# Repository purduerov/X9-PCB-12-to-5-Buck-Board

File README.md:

# X9-PCB-Power-Conversion

The 48V to 12V buck regulator board

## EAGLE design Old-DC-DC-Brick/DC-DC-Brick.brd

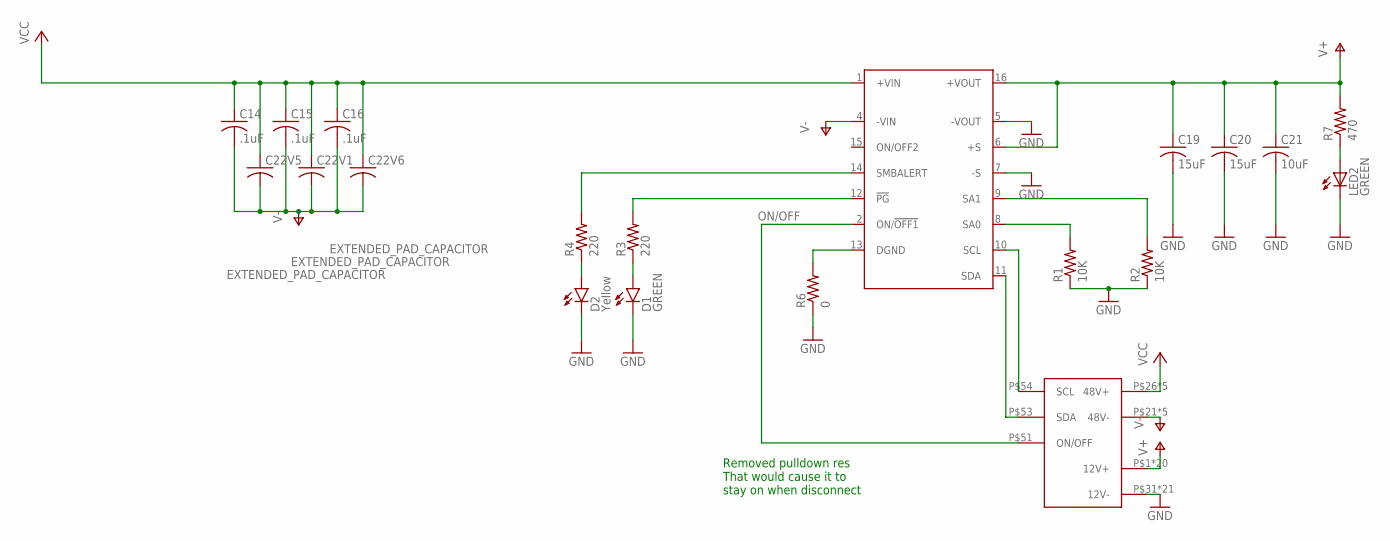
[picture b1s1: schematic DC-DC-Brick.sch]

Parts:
C14, C15, C16: .1uF; C0603
C19, C20: 15uF; C3216
C21: 10uF; C0603
C22V1, C22V5, C22V6: EXTENDED_PAD_CAPACITOR; MODIFIED-NICHICON-UX-8X10
D1: GREEN; LED-0603
D2: Yellow; LED-0603
LED2: GREEN; LED-0603; PARTNO 160-1446-1-ND
R1, R2: 10K; 0603-RES
R3, R4: 220; 0603-RES
R6: 0; 0603-RES
R7: 470; 0603-RES
U$1: BRICK_DC-DC_CONVERTER
U$3: POWER-BRICK-CONNECTOR

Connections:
GND: C19.2, C20.2, C21.2, D1.C, D2.C, LED2.C, R1.1, R2.1, R6.1, U$1.5 (-VOUT), U$1.7 (-S), U$3.P$31 (12V-), U$3.P$32 (12V-), U$3.P$33 (12V-), U$3.P$34 (12V-), U$3.P$35 (12V-), U$3.P$36 (12V-), U$3.P$37 (12V-), U$3.P$38 (12V-), U$3.P$39 (12V-), U$3.P$40 (12V-), U$3.P$41 (12V-), U$3.P$42 (12V-), U$3.P$43 (12V-), U$3.P$44 (12V-), U$3.P$45 (12V-), U$3.P$46 (12V-), U$3.P$47 (12V-), U$3.P$48 (12V-), U$3.P$49 (12V-), U$3.P$50 (12V-), U$3.P$52 (12V-)
unnamed: R2.2, U$1.9 (SA1)
unnamed: R1.2, U$1.8 (SA0)
unnamed: R6.2, U$1.13 (DGND)
unnamed: D1.A, R3.1
unnamed: D2.A, R4.1
unnamed: R4.2, U$1.14 (SMBALERT)
unnamed: R3.2, U$1.12 (!PG)
unnamed: U$1.11 (SDA), U$3.P$53 (SDA)
unnamed: U$1.10 (SCL), U$3.P$54 (SCL)
unnamed: LED2.A, R7.1
ON/OFF: U$1.2 (ON/!OFF1), U$3.P$51 (ON/OFF)
V+: C19.1, C20.1, C21.1, R7.2, U$1.6 (+S), U$1.16 (+VOUT), U$3.P$1 (12V+), U$3.P$2 (12V+), U$3.P$3 (12V+), U$3.P$4 (12V+), U$3.P$5 (12V+), U$3.P$6 (12V+), U$3.P$7 (12V+), U$3.P$8 (12V+), U$3.P$9 (12V+), U$3.P$10 (12V+), U$3.P$11 (12V+), U$3.P$12 (12V+), U$3.P$13 (12V+), U$3.P$14 (12V+), U$3.P$15 (12V+), U$3.P$16 (12V+), U$3.P$17 (12V+), U$3.P$18 (12V+), U$3.P$19 (12V+), U$3.P$20 (12V+)
V-: C14.2, C15.2, C16.2, C22V1.P$1 (4), C22V5.P$1 (4), C22V6.P$1 (4), U$1.4 (-VIN), U$3.P$21 (48V-), U$3.P$22 (48V-), U$3.P$23 (48V-), U$3.P$24 (48V-), U$3.P$25 (48V-)
VCC: C14.1, C15.1, C16.1, C22V1.P$3 (3), C22V5.P$3 (3), C22V6.P$3 (3), U$1.1 (+VIN), U$3.P$26 (48V+), U$3.P$27 (48V+), U$3.P$28 (48V+), U$3.P$29 (48V+), U$3.P$30 (48V+)

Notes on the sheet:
Removed pulldown res That would cause it to stay on when disconnect

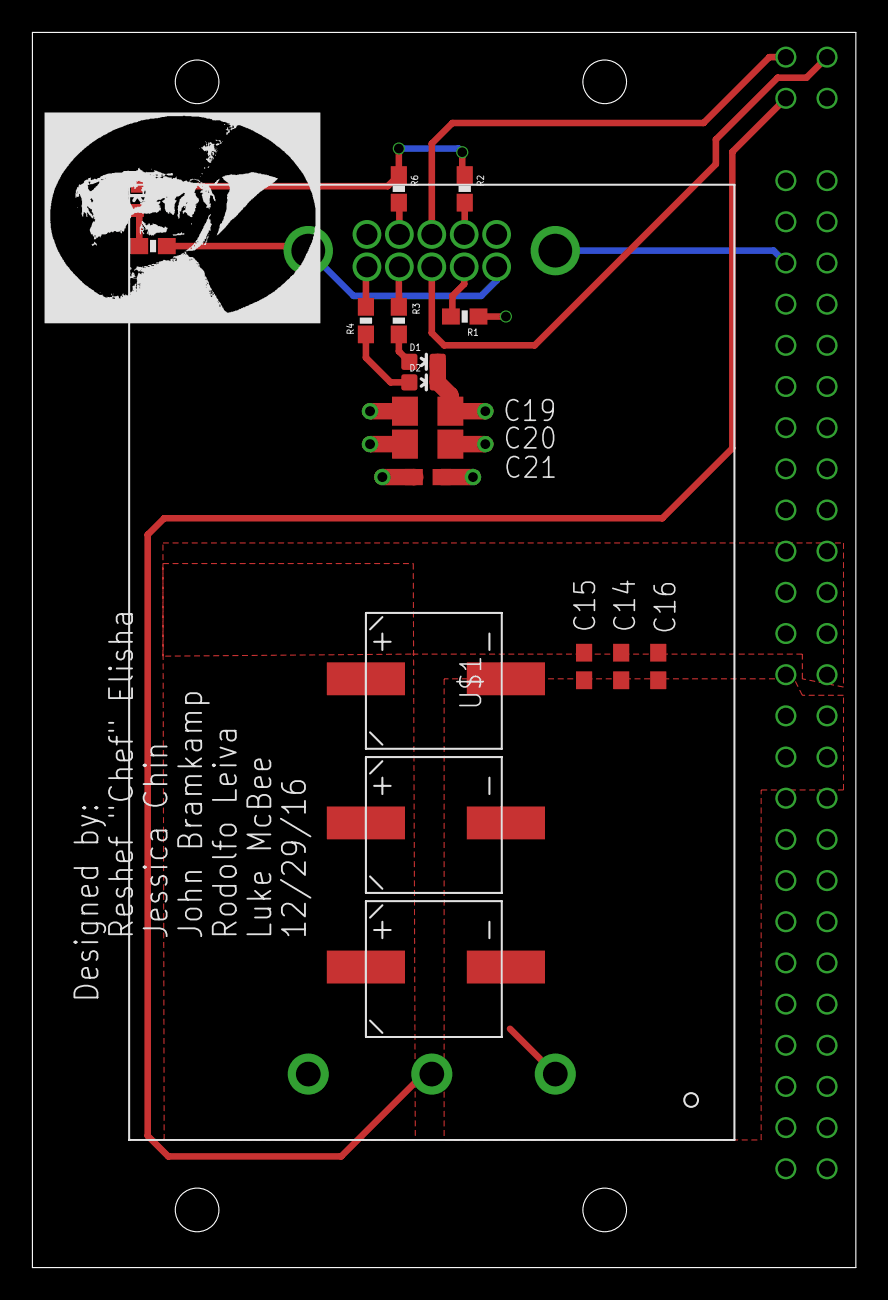
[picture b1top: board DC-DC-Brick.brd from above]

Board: 2 copper layers, 50.8 x 76.2 mm, 20 parts (0 on the bottom side), 15 nets.

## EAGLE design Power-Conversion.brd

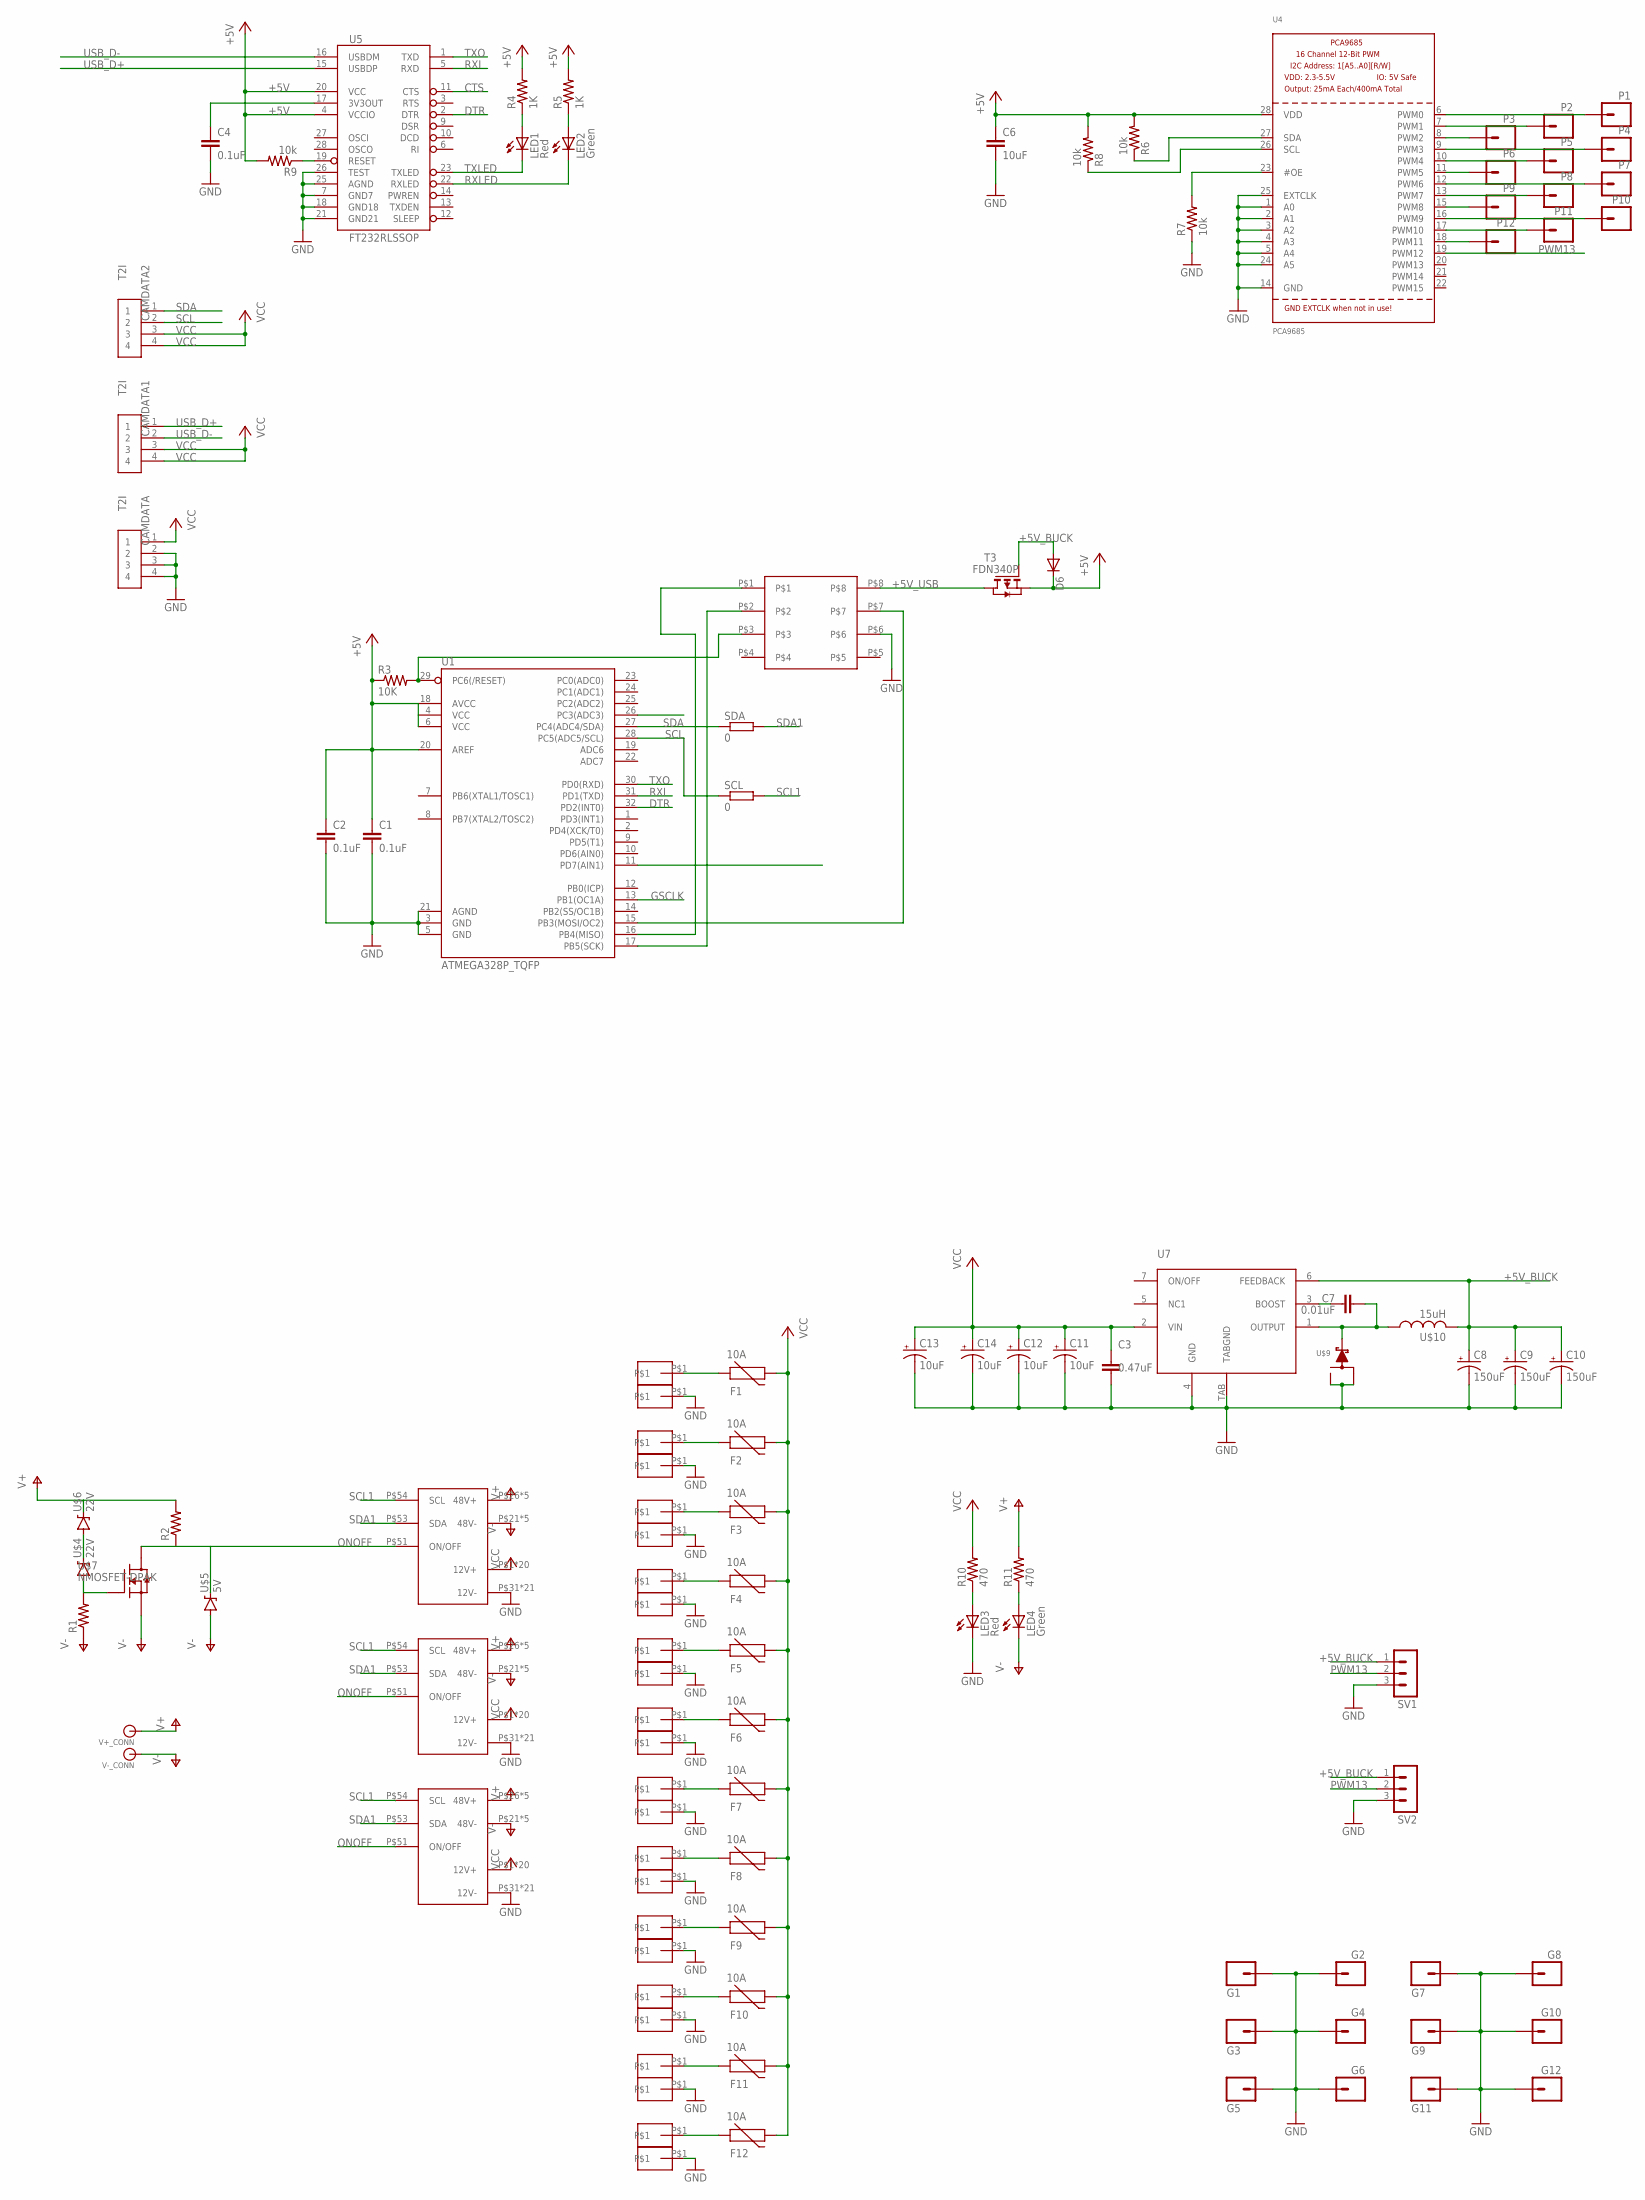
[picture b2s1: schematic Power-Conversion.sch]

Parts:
C1, C2, C4: 0.1uF; 0603-CAP
C3: 0.47uF; C0603
C6: 10uF; 0603-CAP
C7: 0.01uF; 0603-CAP
C8, C9, C10: 150uF; CTAN(7.30_4.30MM)
C11, C12, C13, C14: 10uF; CTAN(7.30_4.30MM)
CAMDATA, CAMDATA1, CAMDATA2: T2I
D6: DIODE-DO-214AC; DO-214AC
F1, F2, F3, F4, F5, F6, F7, F8, F9, F10, F11, F12: 10A; PTC-2920
G1, G2, G3, G4, G5, G6, G7, G8, G9, G10, G11, G12: M01PTH; 1X01
LED1, LED3: Red; LED-0603
LED2, LED4: Green; LED-0603
P1, P2, P3, P4, P5, P6, P7, P8, P9, P10, P11, P12: M01PTH; 1X01
R1, R2: RESISTOR0603-RES; 0603-RES
R3: 10K; 0603-RES
R4, R5: 1K; R0603
R6, R7, R8: 10k; 0603-RES
R9: 10k; 0402-RES
R10, R11: 470; R0603
SCL: 0; R0603
SDA: 0; R0603
SV1, SV2: MA03-1
T3: FDN340P; SOT-23
U1: ATMEGA328P_TQFP; TQFP32-08
U4: PCA9685; TSSOP28
U5: FT232RLSSOP; SSOP28DB
U7: LM2678
U$1, U$2, U$3: POWER-BRICK-CONNECTOR
U$4, U$6: 22V; SOT23-3
U$5: 5V; SOT23-3
U$7: NMOSFET-DPAK; DPAK
U$8: 8_PIN_HEADER
U$9: SWITCHMODE_SCHOTTKY; DPAK-3
U$10: 15uH; HCMA1305
V+_CONN: BANANA_CONN
V+_ESC1, V+_ESC2, V+_ESC3, V+_ESC4, V+_ESC5, V+_ESC6, V+_ESC7, V+_ESC8, V+_ESC9, V+_ESC10, V+_ESC11, V+_ESC12: 16_GUAGE_WIRE
V-_CONN: BANANA_CONN
V-_ESC1, V-_ESC2, V-_ESC3, V-_ESC4, V-_ESC5, V-_ESC6, V-_ESC7, V-_ESC8, V-_ESC9, V-_ESC10, V-_ESC11, V-_ESC12: 16_GUAGE_WIRE

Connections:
+5V: C1.1, C2.1, C6.1, D6.C, R3.1, R4.2, R5.2, R6.2, R8.2, R9.2, T3.2 (S), U1.4 (VCC), U1.6 (VCC), U1.18 (AVCC), U1.20 (AREF), U4.28 (VDD), U5.4 (VCCIO), U5.20 (VCC)
+5V_BUCK: C8.+, C9.+, C10.+, D6.A, SV1.1, SV2.1, T3.3 (G), U7.6 (FEEDBACK), U$10.P$2 (2)
+5V_USB: T3.1 (D), U$8.P$8
CTS: U1.26 (PC3(ADC3)), U5.11 (CTS)
DTR: U1.32 (PD2(INT0)), U5.2 (DTR)
GND: C1.2, C2.2, C3.2, C4.2, C6.2, C8.-, C9.-, C10.-, C11.-, C12.-, C13.-, C14.-, CAMDATA.2, CAMDATA.3, CAMDATA.4, G1.1, G2.1, G3.1, G4.1, G5.1, G6.1, G7.1, G8.1, G9.1, G10.1, G11.1, G12.1, LED3.C, R7.1, SV1.3, SV2.3, U1.3 (GND), U1.5 (GND), U1.21 (AGND), U4.1 (A0), U4.2 (A1), U4.3 (A2), U4.4 (A3), U4.5 (A4), U4.14 (GND), U4.24 (A5), U4.25 (EXTCLK), U5.7 (GND7), U5.18 (GND18), U5.21 (GND21), U5.25 (AGND), U5.26 (TEST), U7.4 (GND), U7.TAB (TABGND), U$1.P$31 (12V-), U$1.P$32 (12V-), U$1.P$33 (12V-), U$1.P$34 (12V-), U$1.P$35 (12V-), U$1.P$36 (12V-), U$1.P$37 (12V-), U$1.P$38 (12V-), U$1.P$39 (12V-), U$1.P$40 (12V-), U$1.P$41 (12V-), U$1.P$42 (12V-), U$1.P$43 (12V-), U$1.P$44 (12V-), U$1.P$45 (12V-), U$1.P$46 (12V-), U$1.P$47 (12V-), U$1.P$48 (12V-), U$1.P$49 (12V-), U$1.P$50 (12V-), U$1.P$52 (12V-), U$2.P$31 (12V-), U$2.P$32 (12V-), U$2.P$33 (12V-), U$2.P$34 (12V-), U$2.P$35 (12V-), U$2.P$36 (12V-), U$2.P$37 (12V-), U$2.P$38 (12V-), U$2.P$39 (12V-), U$2.P$40 (12V-), U$2.P$41 (12V-), U$2.P$42 (12V-), U$2.P$43 (12V-), U$2.P$44 (12V-), U$2.P$45 (12V-), U$2.P$46 (12V-), U$2.P$47 (12V-), U$2.P$48 (12V-), U$2.P$49 (12V-), U$2.P$50 (12V-), U$2.P$52 (12V-), U$3.P$31 (12V-), U$3.P$32 (12V-), U$3.P$33 (12V-), U$3.P$34 (12V-), U$3.P$35 (12V-), U$3.P$36 (12V-), U$3.P$37 (12V-), U$3.P$38 (12V-), U$3.P$39 (12V-), U$3.P$40 (12V-), U$3.P$41 (12V-), U$3.P$42 (12V-), U$3.P$43 (12V-), U$3.P$44 (12V-), U$3.P$45 (12V-), U$3.P$46 (12V-), U$3.P$47 (12V-), U$3.P$48 (12V-), U$3.P$49 (12V-), U$3.P$50 (12V-), U$3.P$52 (12V-), U$8.P$6, U$9.P$1, U$9.P$3, V-_ESC1.P$1, V-_ESC2.P$1, V-_ESC3.P$1, V-_ESC4.P$1, V-_ESC5.P$1, V-_ESC6.P$1, V-_ESC7.P$1, V-_ESC8.P$1, V-_ESC9.P$1, V-_ESC10.P$1, V-_ESC11.P$1, V-_ESC12.P$1
GSCLK: U1.13 (PB1(OC1A))
unnamed: F1.1, V+_ESC1.P$1
unnamed: P11.1, U4.17 (PWM10)
unnamed: F2.1, V+_ESC2.P$1
unnamed: P12.1, U4.18 (PWM11)
unnamed: F3.1, V+_ESC3.P$1
unnamed: F5.1, V+_ESC5.P$1
unnamed: F6.1, V+_ESC6.P$1
unnamed: F7.1, V+_ESC7.P$1
unnamed: U$4.3 (C), U$6.1 (A)
unnamed: R1.2, U$4.1 (A), U$7.1 (G)
unnamed: F8.1, V+_ESC8.P$1
unnamed: LED1.A, R4.1
unnamed: R3.2, U1.29 (PC6(/RESET)), U$8.P$3
unnamed: LED2.A, R5.1
unnamed: P1.1, U4.6 (PWM0)
unnamed: P2.1, U4.7 (PWM1)
unnamed: P3.1, U4.8 (PWM2)
unnamed: P4.1, U4.9 (PWM3)
unnamed: P5.1, U4.10 (PWM4)
unnamed: P6.1, U4.11 (PWM5)
unnamed: P7.1, U4.12 (PWM6)
unnamed: P8.1, U4.13 (PWM7)
unnamed: P9.1, U4.15 (PWM8)
unnamed: P10.1, U4.16 (PWM9)
unnamed: C7.1, U7.3 (BOOST)
unnamed: U1.15 (PB3(MOSI/OC2)), U$8.P$7
unnamed: F9.1, V+_ESC9.P$1
unnamed: U1.16 (PB4(MISO)), U$8.P$1
unnamed: F10.1, V+_ESC10.P$1
unnamed: U1.17 (PB5(SCK)), U$8.P$2
unnamed: F4.1, V+_ESC4.P$1
unnamed: F11.1, V+_ESC11.P$1
unnamed: F12.1, V+_ESC12.P$1
unnamed: R7.2, U4.23 (#OE)
unnamed: C7.2, U7.1 (OUTPUT), U$9.P$4, U$10.P$1 (1)
unnamed: C4.1, U5.17 (3V3OUT)
unnamed: R9.1, U5.19 (RESET)
unnamed: LED3.A, R10.1
unnamed: LED4.A, R11.1
ONOFF: R2.1, U$1.P$51 (ON/OFF), U$2.P$51 (ON/OFF), U$3.P$51 (ON/OFF), U$5.3 (C), U$7.4 (D1)
PWM13: SV1.2, SV2.2, U4.19 (PWM12)
RXI: U1.31 (PD1(TXD)), U5.5 (RXD)
RXLED: LED2.C, U5.22 (RXLED)
SCL: CAMDATA2.2, R8.1, SCL.1, U1.28 (PC5(ADC5/SCL)), U4.26 (SCL)
SCL1: SCL.2, U$1.P$54 (SCL), U$2.P$54 (SCL), U$3.P$54 (SCL)
SDA: CAMDATA2.1, R6.1, SDA.1, U1.27 (PC4(ADC4/SDA)), U4.27 (SDA)
SDA1: SDA.2, U$1.P$53 (SDA), U$2.P$53 (SDA), U$3.P$53 (SDA)
TXLED: LED1.C, U5.23 (TXLED)
TXO: U1.30 (PD0(RXD)), U5.1 (TXD)
USB_D+: CAMDATA1.1, U5.15 (USBDP)
USB_D-: CAMDATA1.2, U5.16 (USBDM)
V+: R2.2, R11.2, U$1.P$26 (48V+), U$1.P$27 (48V+), U$1.P$28 (48V+), U$1.P$29 (48V+), U$1.P$30 (48V+), U$2.P$26 (48V+), U$2.P$27 (48V+), U$2.P$28 (48V+), U$2.P$29 (48V+), U$2.P$30 (48V+), U$3.P$26 (48V+), U$3.P$27 (48V+), U$3.P$28 (48V+), U$3.P$29 (48V+), U$3.P$30 (48V+), U$6.3 (C), V+_CONN.P$1
V-: LED4.C, R1.1, U$1.P$21 (48V-), U$1.P$22 (48V-), U$1.P$23 (48V-), U$1.P$24 (48V-), U$1.P$25 (48V-), U$2.P$21 (48V-), U$2.P$22 (48V-), U$2.P$23 (48V-), U$2.P$24 (48V-), U$2.P$25 (48V-), U$3.P$21 (48V-), U$3.P$22 (48V-), U$3.P$23 (48V-), U$3.P$24 (48V-), U$3.P$25 (48V-), U$5.1 (A), U$7.3 (S), V-_CONN.P$1
VCC: C3.1, C11.+, C12.+, C13.+, C14.+, CAMDATA.1, CAMDATA1.3, CAMDATA1.4, CAMDATA2.3, CAMDATA2.4, F1.2, F2.2, F3.2, F4.2, F5.2, F6.2, F7.2, F8.2, F9.2, F10.2, F11.2, F12.2, R10.2, U7.2 (VIN), U$1.P$1 (12V+), U$1.P$2 (12V+), U$1.P$3 (12V+), U$1.P$4 (12V+), U$1.P$5 (12V+), U$1.P$6 (12V+), U$1.P$7 (12V+), U$1.P$8 (12V+), U$1.P$9 (12V+), U$1.P$10 (12V+), U$1.P$11 (12V+), U$1.P$12 (12V+), U$1.P$13 (12V+), U$1.P$14 (12V+), U$1.P$15 (12V+), U$1.P$16 (12V+), U$1.P$17 (12V+), U$1.P$18 (12V+), U$1.P$19 (12V+), U$1.P$20 (12V+), U$2.P$1 (12V+), U$2.P$2 (12V+), U$2.P$3 (12V+), U$2.P$4 (12V+), U$2.P$5 (12V+), U$2.P$6 (12V+), U$2.P$7 (12V+), U$2.P$8 (12V+), U$2.P$9 (12V+), U$2.P$10 (12V+), U$2.P$11 (12V+), U$2.P$12 (12V+), U$2.P$13 (12V+), U$2.P$14 (12V+), U$2.P$15 (12V+), U$2.P$16 (12V+), U$2.P$17 (12V+), U$2.P$18 (12V+), U$2.P$19 (12V+), U$2.P$20 (12V+), U$3.P$1 (12V+), U$3.P$2 (12V+), U$3.P$3 (12V+), U$3.P$4 (12V+), U$3.P$5 (12V+), U$3.P$6 (12V+), U$3.P$7 (12V+), U$3.P$8 (12V+), U$3.P$9 (12V+), U$3.P$10 (12V+), U$3.P$11 (12V+), U$3.P$12 (12V+), U$3.P$13 (12V+), U$3.P$14 (12V+), U$3.P$15 (12V+), U$3.P$16 (12V+), U$3.P$17 (12V+), U$3.P$18 (12V+), U$3.P$19 (12V+), U$3.P$20 (12V+)

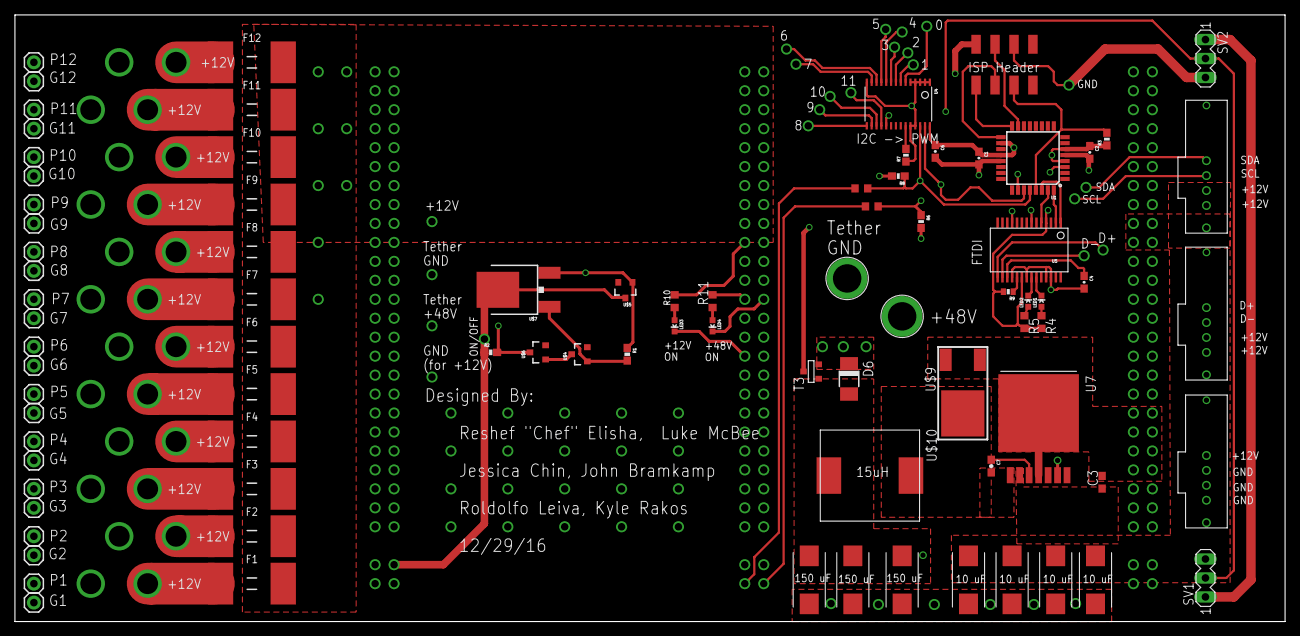
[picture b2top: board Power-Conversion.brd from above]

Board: 4 copper layers, 170.2 x 81.3 mm, 113 parts (0 on the bottom side), 60 nets.

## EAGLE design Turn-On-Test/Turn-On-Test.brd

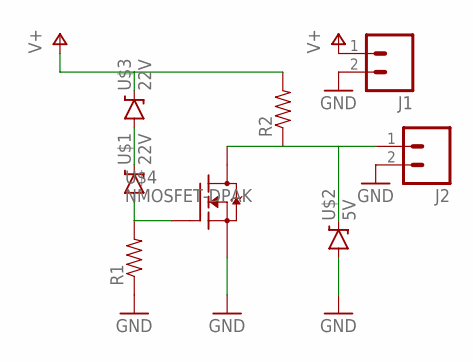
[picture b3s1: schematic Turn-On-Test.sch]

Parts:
J1, J2: M02PTH; 1X02
R1, R2: RESISTOR0603-RES; 0603-RES
U$1, U$3: 22V; SOT23-3
U$2: 5V; SOT23-3
U$4: NMOSFET-DPAK; DPAK

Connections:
GND: J1.2, J2.2, R1.1, U$2.1 (A), U$4.3 (S)
unnamed: U$1.3 (C), U$3.1 (A)
unnamed: R1.2, U$1.1 (A), U$4.1 (G)
unnamed: J2.1, R2.1, U$2.3 (C), U$4.4 (D1)
V+: J1.1, R2.2, U$3.3 (C)

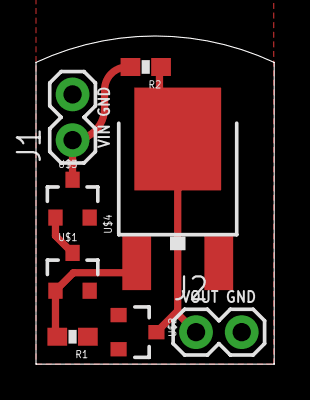
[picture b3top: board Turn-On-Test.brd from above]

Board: 2 copper layers, 13.2 x 18.2 mm, 8 parts (0 on the bottom side), 5 nets.

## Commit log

2016-10-04 Initial gitignore and readme
2016-10-22 init eagle.epf
2016-10-22 Create a Power Conversion Schematic
2016-10-22 Finish Prelim Brick Schematic
2016-10-22 Finsh DC-DC Brick Board
2016-10-25 Created Schematic
2016-10-26 Created Board Layout and Changed Schematics
2016-10-29 Worked on Board Layout
2016-10-29 create test schematic
2016-10-30 Test schematic done
2016-10-30 Layout done
2016-10-30 finalized back silk
2016-11-02 created CAM job
2016-11-02 release01
2016-11-03 Worked on new part
2016-11-05 Worked on DC-DC Board layout
2016-11-07 Board Layout
2016-11-08 progress
2016-11-09 Fixed some routing and added resistor
    Added resistor between ON/OFF pin and V-. The resistor's value is not
    necessarily the value we will end up using.
2016-11-10 prelim sch
2016-11-10 gen brd
2016-11-12 2 layer power input/output
2016-11-12 small correction
2016-11-12 closer connectors
2016-11-12 Worked on power polygons
2016-11-13 Updated polygons again
2016-11-13 saturday
2016-11-16 cleaned up poligons
2016-11-19 Fuse and prelim MCU connections
2016-11-23 Placement and early routing of AVR board
2016-11-24 pwm routing
2016-11-25 more routing
2016-11-25 layer stackup+more routing
2016-11-28 prelim routing done
2016-11-28 aesthetics and gnd separation
2016-11-29 ESC Silk
2016-11-29 add 1"
2016-11-30 stuffs
2016-11-30 added John purdue silk screen
2016-12-04 Fuse
2016-12-04 Silkscreen Adjustment
    moved LED and Silkscreen slightly
2016-12-04 Here goes nothin
2016-12-04 redesign
2016-12-06 fixed
    fixed small error
2016-12-07 FIxed connection issue
    Gnd not connected in J purdue eye LED - fixed
2016-12-21 Replaced normal fuses with individual PTC fuses
2016-12-22 After 8 hours of continuous work, I am 90% done with the power distribution board
2016-12-22 Finished most of the wiring. Also changed pwm chips and FTDI chips
2016-12-24 More changes to the board layout. Should be complete.
2016-12-24 Added pull up resistors to I2C lines
2016-12-27 Changes made to DC bricks (see Google Doc)
2016-12-28 Switched from a linear regulator to a buck regulator
2016-12-30 Fixed most suggestions from Michael. Also added some cosmetic changes
2016-12-30 Added silkscreen
2016-12-30 Added debugging pins and more silk screen
2016-12-30 Fixed problem with gnd via
2017-01-02 Fixed a few silkscrean problems
2017-01-25 Added new folder
    new 1/8th brick and 1/4 brick files
2017-01-26 Created new board for quarter brick
    made new board for quarter brick to be used
2017-01-26 stuff
2017-01-30 completed 1/4 brick
    finished redesign of the 1/4 power brick board
2017-01-30 redesigned 1/4 brick board
    redesigned quarter brick (and 1/8th brick) board
2017-01-30 Completed brick board
    hoot
2017-01-30 renamed files
    fixed possible confusion with file names

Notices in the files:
parts and their libraries:
SparkFun-Resistors: Licensing: Creative Commons ShareAlike 4.0 International - https://creativecommons.org/licenses/by-sa/4.0
SparkFun: Licensing: CC v3.0 Share-Alike You are welcome to use this library for commercial purposes.
